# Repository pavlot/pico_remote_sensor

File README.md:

# RPi Pico remote sensor shield
[Raspberry Pi Pico](https://www.raspberrypi.com/products/raspberry-pi-pico/) shield for sensors and wireless data transfer with [RFM75 2.4GHz radiomodule](https://www.hoperf.com/modules/2.4g/RFM75.html)

## Firmware installation
This shield has example firmware to transmit and reaceive data.
Before any scripts uploaded [Micropython must be installed](https://micropython.org/download/rp2-pico/) to you RPi pico board

### Install from github
If you wand just to run firmware and check how it works, the easiest way is to install it as package
You will need [mpremote](https://docs.micropython.org/en/latest/reference/mpremote.html) tool to perform this operation.
After you board connected to usb and MicroPython installed execute:
```bash
mpremote.py mip install https://raw.githubusercontent.com/pavlot/pico_remote_sensor/main/firmware/package.json
```
This will install firmware package and required dependencies to your board.

This firmware shipped with two modules: transmitter and receiver.

Open Micropython REPL session with  
```bash
mpremote.py
```
and execute
```python
from firmware import receiver
```
On console you should see something like:
```
INFO:root:TX part started
INFO:root:----  Starting module initialisation ------
INFO:root:Is RFMx chip connected: True
INFO:root:Chip id: 63000000
INFO:root:RF channel set to 4
INFO:root:LNA gain set to high
INFO:root:Data rate is: 250ksps
INFO:root:Adress width binary value: 11
INFO:root:Pipe 0 enabled
INFO:root:RX_Pipe 0 address set to 1122332211
INFO:root:PipeAddr after set: 1122332211
INFO:root:PipeAddr: 1122332211
INFO:root:Pipe 0 RX payload width is 5
INFO:root:Auto acknowledge disabled
INFO:root:CRC encoding scheme 2 bytes
INFO:root:CRC enabled
INFO:root:RFx module power up
INFO:root:----  Module initialisation done ------
INFO:root:----  Starting main receive loop ------
```
it means that rx part is ready to receive data. Default implementation will output all receivet data as hex values to INFO logger, e.g.
```
INFO:root:Data received: cafeb0ba01
```

Same procedure for transmitter, inside REPL session:
```
from firmware import transmitter
```

Transmitter expects SHT30 sensor to be connected to I2C0 bus and continuosly read it's values sending them to the air.
Also transmitted values logged to the INFO logger

### Autostart
If you want that transmitter or receiver start on board startup you have to create main.py in the root foldef of board filesystem.

To simplify this procedure install_* modules shipped with firmware.

For example, if you want to make trasmitter: inside mpremote REPL console execute
```
from firmware import install_transmitter
```
and reboot with `Ctrl+]` or switch-off/switch-on your device. This will make it transmitting sensor data without any human interaction.

Now you can poweron it from USB charger and place at bathroom, data will be transfered automatically.

### Development
If you want to implement own logic, change configuration or write everything from scratch you can clone this repository and mount source directory like
```shell
mpremote.py mount src
``` 
All changes you will do will be immidiately available on your board.

Only remember to perform Soft reboot befor re-importing any modules

This firmware depends on [pyRFTdi](https://github.com/pavlot/pyrftdi) module. This dependencies could be installed like:
```
mpremote mip install https://raw.githubusercontent.com/pavlot/pyrftdi/RPPico/package.json
```

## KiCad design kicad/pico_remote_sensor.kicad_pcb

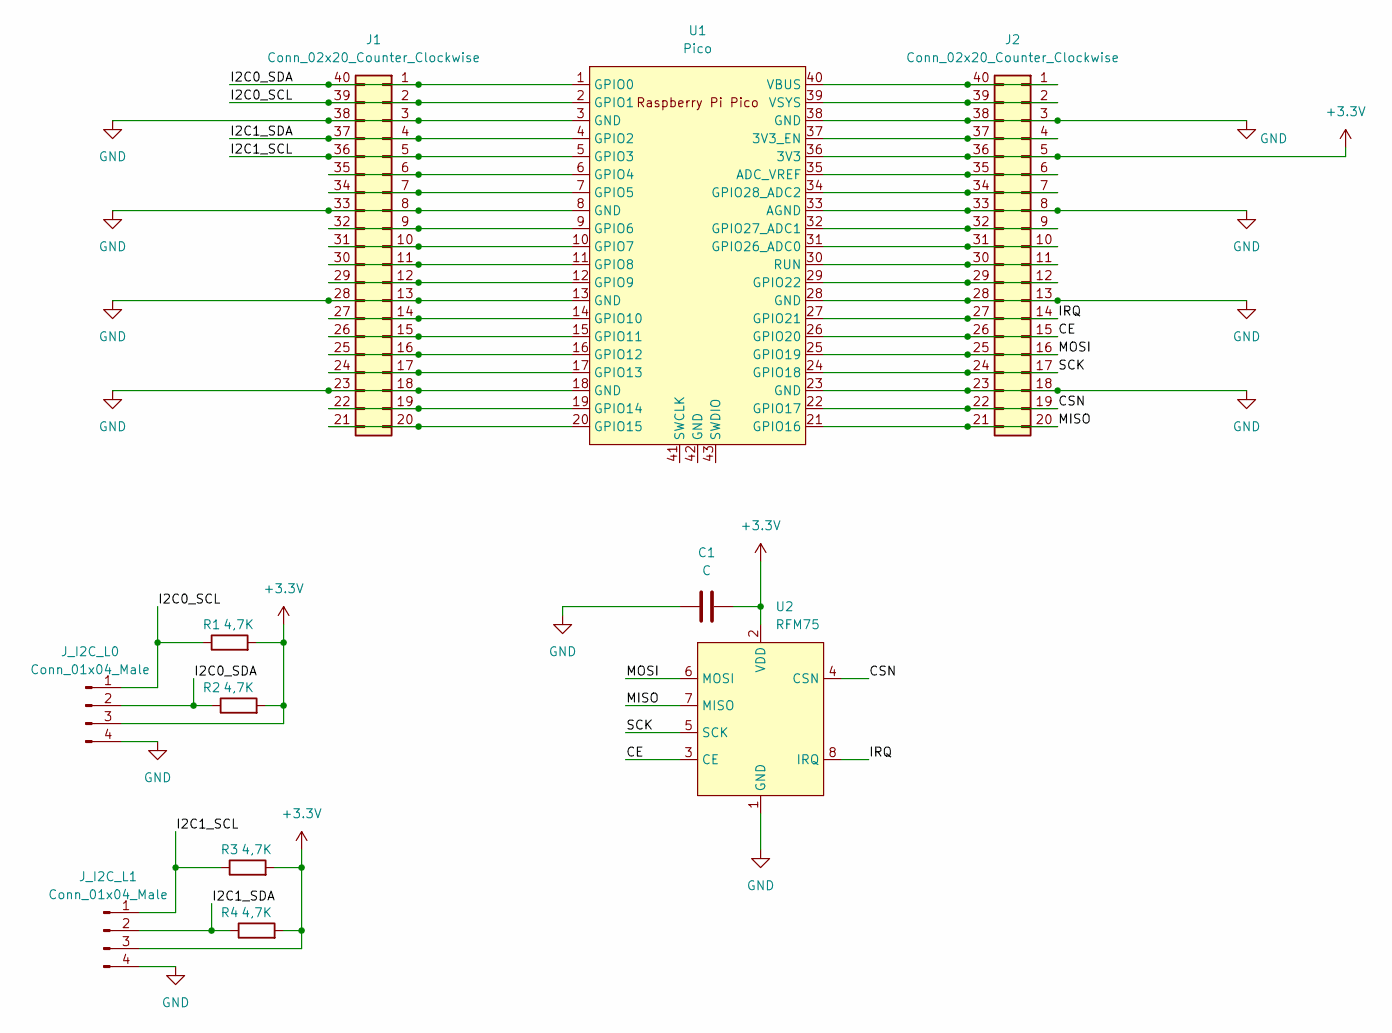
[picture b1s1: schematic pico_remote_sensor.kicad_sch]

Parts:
C1: C; C_1206_3216Metric_Pad1.33x1.80mm_HandSolder
J1, J2: Conn_02x20_Counter_Clockwise; PinHeader_2x20_P2.54mm_Vertical
J_I2C_L0, J_I2C_L1: Conn_01x04_Male; PinHeader_1x04_P2.00mm_Vertical
R1, R2, R3, R4: 4,7K; R_1206_3216Metric_Pad1.30x1.75mm_HandSolder
U1: Pico; RPi_Pico_SMD_TH
U2: RFM75

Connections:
+3V3: C1.1, J2.5, J2.36, J_I2C_L0.3, J_I2C_L1.3, R1.2, R2.2, R3.2, R4.2, U1.36 (3V3), U2.2 (VDD)
/CE: J2.15, J2.26, U1.26 (GPIO20), U2.3 (CE)
/CSN: J2.19, J2.22, U1.22 (GPIO17), U2.4 (CSN)
/I2C0_SCL: J1.2, J1.39, J_I2C_L0.1, R1.1, U1.2 (GPIO1)
/I2C0_SDA: J1.1, J1.40, J_I2C_L0.2, R2.1, U1.1 (GPIO0)
/I2C1_SCL: J1.5, J1.36, J_I2C_L1.1, R3.1, U1.5 (GPIO3)
/I2C1_SDA: J1.4, J1.37, J_I2C_L1.2, R4.1, U1.4 (GPIO2)
/IRQ: J2.14, J2.27, U1.27 (GPIO21), U2.8 (IRQ)
/MISO: J2.20, J2.21, U1.21 (GPIO16), U2.7 (MISO)
/MOSI: J2.16, J2.25, U1.25 (GPIO19), U2.6 (MOSI)
/SCK: J2.17, J2.24, U1.24 (GPIO18), U2.5 (SCK)
GND: C1.2, J1.3, J1.8, J1.13, J1.18, J1.23, J1.28, J1.33, J1.38, J2.3, J2.8, J2.13, J2.18, J2.23, J2.28, J2.33, J2.38, J_I2C_L0.4, J_I2C_L1.4, U1.3 (GND), U1.8 (GND), U1.13 (GND), U1.18 (GND), U1.23 (GND), U1.28 (GND), U1.33 (AGND), U1.38 (GND), U2.1 (GND)
unnamed: J1.6, J1.35, U1.6 (GPIO4)
unnamed: J1.7, J1.34, U1.7 (GPIO5)
unnamed: J1.9, J1.32, U1.9 (GPIO6)
unnamed: J1.10, J1.31, U1.10 (GPIO7)
unnamed: J1.11, J1.30, U1.11 (GPIO8)
unnamed: J1.12, J1.29, U1.12 (GPIO9)
unnamed: J1.14, J1.27, U1.14 (GPIO10)
unnamed: J1.15, J1.26, U1.15 (GPIO11)
unnamed: J1.16, J1.25, U1.16 (GPIO12)
unnamed: J1.17, J1.24, U1.17 (GPIO13)
unnamed: J1.19, J1.22, U1.19 (GPIO14)
unnamed: J1.20, J1.21, U1.20 (GPIO15)
unnamed: J2.12, J2.29, U1.29 (GPIO22)
unnamed: J2.11, J2.30, U1.30 (RUN)
unnamed: J2.10, J2.31, U1.31 (GPIO26_ADC0)
unnamed: J2.9, J2.32, U1.32 (GPIO27_ADC1)
unnamed: J2.7, J2.34, U1.34 (GPIO28_ADC2)
unnamed: J2.6, J2.35, U1.35 (ADC_VREF)
unnamed: J2.4, J2.37, U1.37 (3V3_EN)
unnamed: J2.2, J2.39, U1.39 (VSYS)
unnamed: J2.1, J2.40, U1.40 (VBUS)

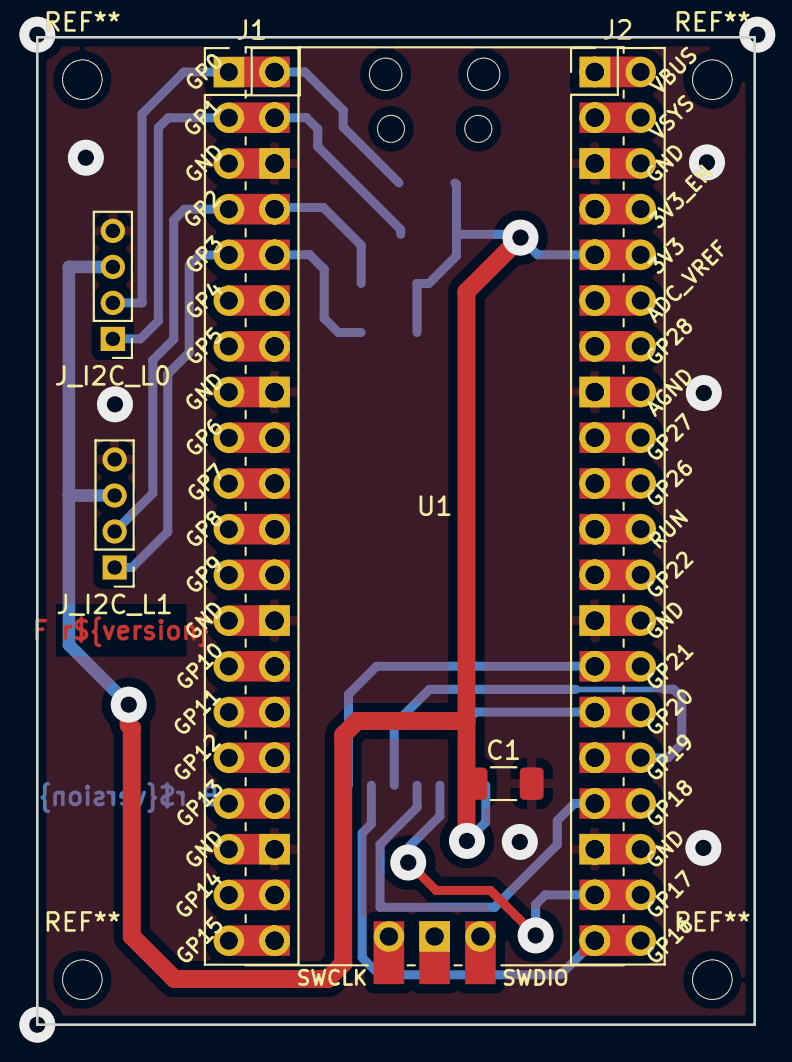
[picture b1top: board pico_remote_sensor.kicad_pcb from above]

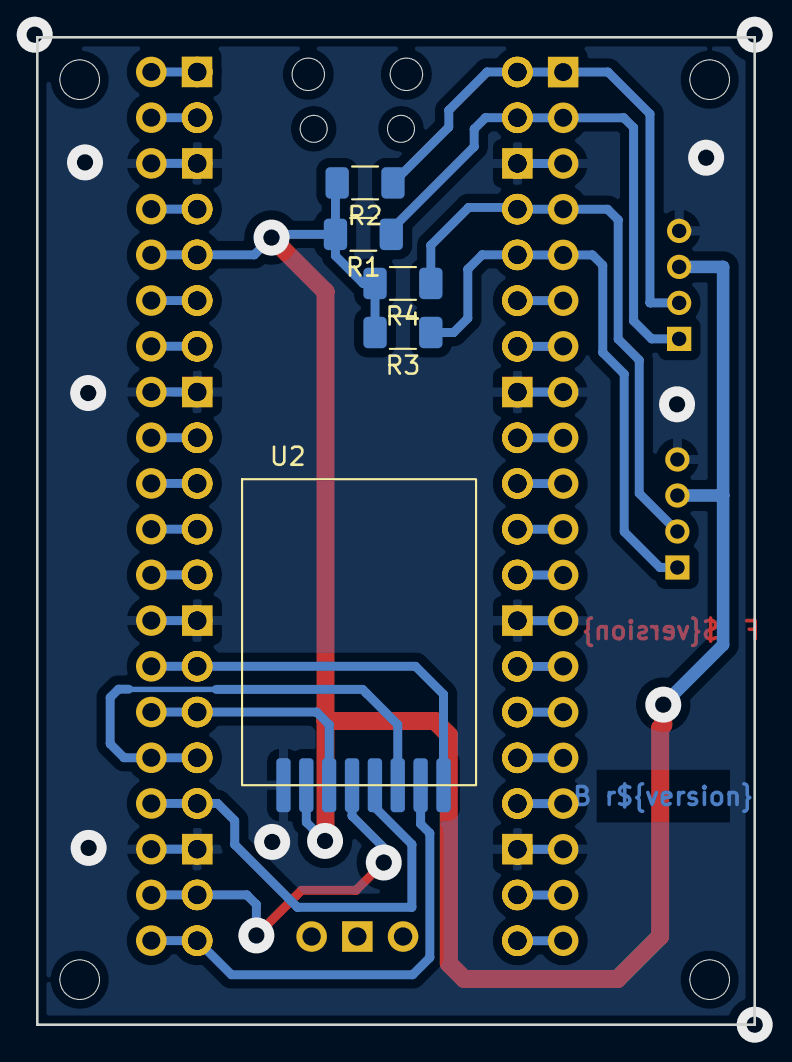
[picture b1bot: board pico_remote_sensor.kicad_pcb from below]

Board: 2 copper layers, 39.9 x 54.9 mm, 11 parts (5 on the bottom side), 33 nets.

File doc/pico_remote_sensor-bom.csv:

Row,Description,Part,References,Value,Footprint,Quantity Per PCB,Status,Datasheet
1,Unpolarized capacitor,C,C1,C,C_1206_3216Metric_Pad1.33x1.80mm_HandSolder,1, ,~
2,"Generic connector, double row, 02x20, counter clockwise pin numbering scheme (similar to DIP packge numbering), script generated (kicad-library-utils/schlib/autogen/connector/)",Conn_02x20_Counter_Clockwise,J1 J2,Conn_02x20_Counter_Clockwise,PinHeader_2x20_P2.54mm_Vertical,2, ,~
3,"Generic connector, single row, 01x04, script generated (kicad-library-utils/schlib/autogen/connector/)",Conn_01x04_Male,J_I2C_L0 J_I2C_L1,Conn_01x04_Male,PinHeader_1x04_P2.00mm_Vertical,2, ,~
4,Resistor,R,R1 R2 R3 R4,"4,7K",R_1206_3216Metric_Pad1.30x1.75mm_HandSolder,4, ,~
5,,Pico,U1,Pico,RPi_Pico_SMD_TH,1, ,
6,,RFM75,U2,RFM75,RFM75,1, ,





Project info:
Schematic:,pico_remote_sensor
Variant:,default
Revision:,
Date:,2023-04-22_11-45-25
KiCad Version:,6.0.2+dfsg-1
Statistics:
Component Groups:,6
Component Count:,11
Fitted Components:,11
Number of PCBs:,1
Total Components:,11

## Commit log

2023-04-22 Schematics imported
2023-04-22 Photoresisting production added
2023-04-22 Board versions added
2023-04-22 Drilling implemented
2023-04-22 Edge cuts
2023-04-22 Cleanup
2023-04-22 docs
2023-04-22 firmware
2023-04-24 pyrftdi link corrected
    Add the correct hyperlink to [pyRFTdi](https://github.com/pavlot/pyrftdi) module.
